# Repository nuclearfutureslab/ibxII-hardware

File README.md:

# IBX ]\[ Hardware

IBX ]\[ is an information barrier setup for nuclear warhead verification with an Apple II ([Details](http://www.vintageverification.org)).
This repository contains schematics and layout files for two custom Apple II peripheral cards.

The KiCad files use the [Apple \]\[ Edge Connector Template](http://www.xjmaas.nl/my-apple-collection/apple-edge-connector-template-for-kicad/), best place it inside the directory as (Apple2_Bus).

## ADC Board
Apple II peripheral card for A/D conversion of signals from radiation detectors (scintillator/photo multiplier combination). The card includes all necessary parts - pre-amplifier, amplification & pulse shaping, peak-detect and hold circuit, ADC timing circuit. The current revision is improved to use full +12V/-12V components all the way to the ADC. Previous versions included 8 LEDs that can be toggled by writing to a specific Apple II memory location, but these have been removed now.

[Rev. 3 Board at OSHPark repository](https://oshpark.com/shared_projects/9M42SHV2)
[Rev. 1 Board at OSHPark repository](https://oshpark.com/shared_projects/9M42SHV2)

### Address scheme (has to be offset by address of card slot, eg. 49344 for Slot 4):

| Address | R/W | Function |
|----| ----|----|
| 01 | (Read) | Reset trigger circuit, make it ready for a new incoming pulse |
| 02 | (Read) | Read low byte of ADC value |
| 03 | (Read) | Read high byte of ADC value |
| 04 | (Read) | Read status buffer for ADC |

## HV Board

Apple II peripheral card to provide high voltage supply to devices (e.g. Photo Multiplier tubes). The voltage is adjustable by writing an 8bit value to a memory address. It produces a voltage from 0-5V depending on this value, which gets converted into highvoltage by a CAEN 7505P module. 

[Rev. 1 Board at OSHPark repository](https://oshpark.com/shared_projects/YkaW1fvx)

### Address scheme (has to be offset by address of card slot, eg. 49312 for Slot 2):

| Address | R/W | Function |
|----| ----|----|
00 | (Write) | Address to write a value for DA
01 | (Read) | enable HV 
02 | (Read) | disable HV

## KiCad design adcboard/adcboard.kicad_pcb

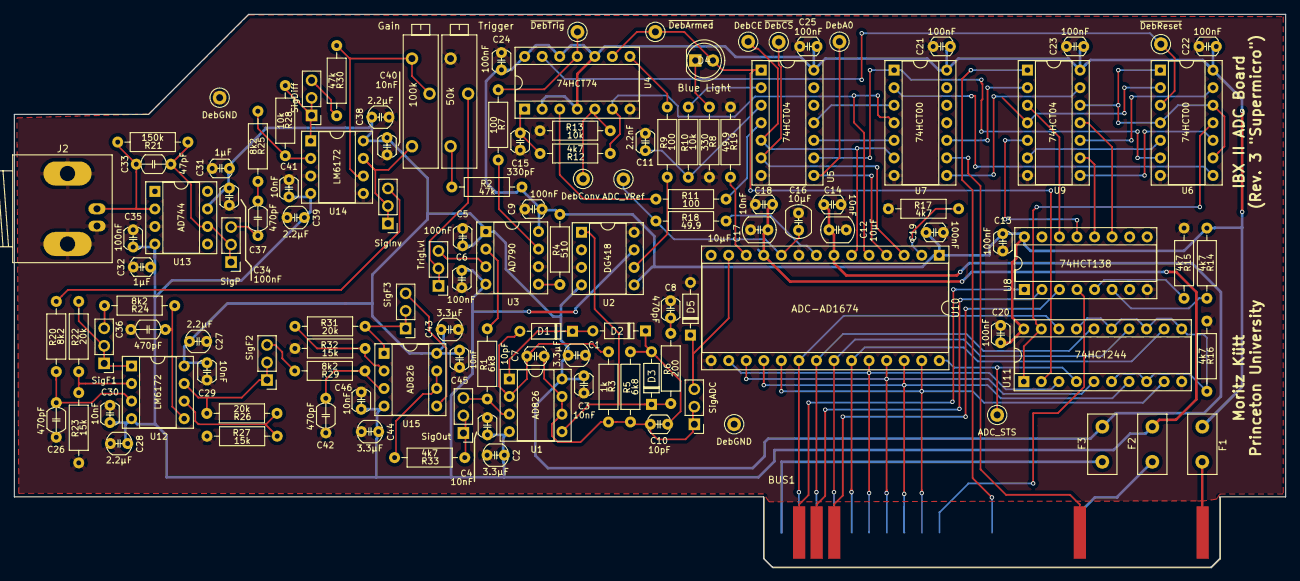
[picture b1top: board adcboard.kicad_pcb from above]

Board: 2 copper layers, 184.0 x 80.0 mm, 126 parts (0 on the bottom side), 99 nets.

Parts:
BUS1: A2_BUS; BUS_ADC
C1, C2, C43, C44: 3.3µF; FG14
C3, C4, C14, C18, C29, C30, C40, C41, C45, C46: 10nF; FG18
C5, C6, C9, C13, C19, C20, C21, C22, C23, C24, C25, C34, C35: 100nF; FG18
C7, C10: 10pF; FG18
C8: 470pF; FG18
C11: 2.2nF; FG18
C12, C16, C17: 10µF; FG16
C15: 330pF; FG18
C26, C36, C37, C42: 470pF; FG28
C27, C28, C38, C39: 2.2µF; FG14
C31, C32: 1µF; FG18
C33: 47pF; FG28
D1, D2, D3: SD103A; D_DO-35_SOD27_P7.62mm_Horizontal
D4: Blue Light; LED_D5.0mm
D5: D_Zener_Small; D_DO-35_SOD27_P7.62mm_Horizontal
F1, F3: HC:250mA; Fuse_Littelfuse_395Series
F2: HC:120mA; Fuse_Littelfuse_395Series
Gain: 100k; Potentiometer_Bourns_3006P_Horizontal
J1: SigOut; 3-Pin-Header
J2: Detector; BNC_Socket_TYCO-AMP_LargePads
J3: TrigLvl; 3-Pin-Header
J4: SigADC; 3-Pin-Header
J5: SigF1; 3-Pin-Header
J6: SigP; 3-Pin-Header
J7: SigF2; 3-Pin-Header
J8: SigDiff; 3-Pin-Header
J9: SigF3; 3-Pin-Header
J10: SigInv; 3-Pin-Header
R1, R5: 6k8; Resistor
R2, R30: 47k; Resistor
R3: 1k; Resistor
R4: 510; Resistor
R6: 200; Resistor
R7, R9, R11: 100; Resistor
R8: 330; Resistor
R10, R13, R28: 10k; Resistor
R12, R14, R15, R16, R17, R33: 4k7; Resistor
R18, R19: 49.9; Resistor
R20, R24, R25, R29: 8k2; Resistor
R21: 150k; Resistor
R22, R26, R31: 20k; Resistor
R23, R27, R32: 15k; Resistor
TP1: ~DebTrig; TP
TP2: ~DebArmed; TP
TP3: ~DebReset; TP
TP4: ADC_VRef; TP
TP5: DebConv; TP
TP6: DebA0; TP
TP7: DebCE; TP
TP8: ~DebCS; TP
TP9, TP10: DebGND; TP
TP11: ADC_STS; TP
Trigger: 50k; Potentiometer_Bourns_3006P_Horizontal
U1, U15: AD826; DIP-8
U2: DG418; DIP-8
U3: AD790; DIP-8
U4: 74HCT74; DIP-14
U5, U9: 74HCT04; DIP-14
U6, U7: 74HCT00; DIP-14
U8: 74HCT138; DIP-16_W7.62mm_Socket
U10: ADC-AD1674; DIP-28_W15.24mm_Socket
U11: 74HCT244; DIP-20_W7.62mm_Socket
U12, U14: LM6172; DIP-8
U13: AD744; DIP-8

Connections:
+5V: C9.2, C13.1, C19.1, C20.2, C21.2, C22.2, C23.2, C24.2, C25.2, F1.1, R2.2, R4.2, R14.1, U2.5, U3.8, U4.2, U4.4, U4.10, U4.12, U4.14, U5.14, U6.14, U7.14, U8.16, U9.14, U10.1, U11.20
+12V: C1.1, C3.2, C5.1, C12.2, C14.1, C27.1, C29.2, C31.1, C34.2, C38.1, C40.2, C43.1, C45.2, F3.2, U1.8, U2.4, U3.1, U10.7, U12.8, U13.7, U14.8, U15.8
-12V: C2.1, C4.2, C6.1, C17.2, C18.1, C28.1, C30.2, C32.1, C35.2, C39.1, C41.2, C44.1, C46.2, F2.2, U1.4, U2.7, U3.4, U10.11, U12.4, U13.4, U14.4, U15.4
/Amplifier/SigDiff: J8.1, J8.2, R28.1, U14.1
/Amplifier/SigDiffb: J8.3, R30.2
/Amplifier/SigF1: J5.1, J5.2, R22.2, U12.1
/Amplifier/SigF1b: J5.3, R24.2
/Amplifier/SigF2: J7.1, J7.2, R26.2, U12.7
/Amplifier/SigF2b: J7.3, R29.2
/Amplifier/SigF3: J9.1, J9.2, R31.2, U15.1
/Amplifier/SigF3b: J9.3, U15.5
/Amplifier/SigInv: Gain.1, J10.1, J10.2, U14.7
/Amplifier/SigInvb: J10.3, R20.2
/Amplifier/SigOut: J1.1, J1.2, R33.1
/Amplifier/SigP: C33.2, J6.1, J6.2, R21.1, U13.6
/Amplifier/SigPb: C37.2, J6.3
/Amplifier/SigRaw: C33.1, J2.1, R21.2, U13.2
A0: BUS1.2, U8.1
A1: BUS1.3, U8.2
A2: BUS1.4, U8.3
D0: BUS1.49, U10.20, U11.18
D1: BUS1.48, U10.21, U11.16
D2: BUS1.47, U10.22, U11.14
D3: BUS1.46, U10.23, U11.12
D4: BUS1.45, U10.16, U10.24, U11.3
D5: BUS1.44, U10.17, U10.25, U11.5
D6: BUS1.43, U10.18, U10.26, U11.7
D7: BUS1.42, U10.19, U10.27, U11.9
GND: BUS1.26, C1.2, C2.2, C3.1, C4.1, C5.2, C6.2, C8.1, C9.1, C11.1, C12.1, C13.2, C14.2, C15.1, C16.1, C17.1, C18.2, C19.2, C20.1, C21.1, C22.1, C23.1, C24.1, C25.1, C26.1, C27.2, C28.2, C29.1, C30.1, C31.2, C32.2, C34.1, C35.1, C36.1, C38.2, C39.2, C40.1, C41.1, C42.1, C43.2, C44.2, C45.1, C46.1, D5.2, J2.2, R8.2, R13.1, R15.1, R16.1, R17.1, R19.1, R23.1, R27.1, R32.1, TP9.1, TP10.1, Trigger.3, U2.3, U2.8, U3.6, U4.7, U5.7, U6.7, U7.7, U8.8, U9.7, U10.9, U10.15, U11.10, U13.3, U14.3, U14.5
unnamed: BUS1.25, F1.2
unnamed: BUS1.33, F2.1
unnamed: BUS1.50, F3.1
unnamed: C7.1, D1.2, R3.1, U1.2
unnamed: C8.2, R6.2
unnamed: C10.1, D2.1, D3.2, R5.2
unnamed: C7.2, C10.2, J4.1, J4.2, R3.2, R5.1, U1.6, U1.7
unnamed: C11.2, R10.1, U5.3
unnamed: C15.2, R12.2, U4.1
unnamed: C16.2, R18.1, TP4.1, U10.10
unnamed: C26.2, R20.1, U12.3
unnamed: C36.2, R24.1, U12.5
unnamed: C37.1, R25.2
unnamed: C42.2, R29.1, U15.3
unnamed: D1.1, D2.2, U1.1
unnamed: D3.1, R6.1, U1.5, U2.1
unnamed: D4.1, R8.1
unnamed: D5.1, J4.3, U10.13
unnamed: J1.3, R1.1, U1.3
unnamed: J3.1, J3.2, Trigger.2
unnamed: J3.3, U3.3
unnamed: R1.2, U3.2
unnamed: R2.1, Trigger.1
unnamed: R4.1, U3.5
unnamed: R7.1, TP1.1, U4.11
unnamed: R7.2, U3.7
unnamed: R9.1, U2.6
unnamed: R9.2, U4.8
unnamed: R10.2, U5.2
unnamed: R11.1, U4.3
unnamed: R11.2, U5.4
unnamed: R12.1, U4.6, U7.4, U10.5
unnamed: R13.2, TP5.1, U4.5
unnamed: R14.2, U8.6
unnamed: R15.2, U8.5
unnamed: R16.2, U11.6, U11.8, U11.11, U11.13, U11.15, U11.17
unnamed: R17.2, U10.2
unnamed: R18.2, U10.8
unnamed: R19.2, U10.12
unnamed: R22.1, R23.2, U12.2
unnamed: R25.1, R28.2, U14.2
unnamed: R26.1, R27.2, U12.6
unnamed: Gain.2, Gain.3, R30.1, U14.6
unnamed: R31.1, R32.2, U15.2
unnamed: R33.2, U15.6, U15.7
unnamed: TP3.1, U4.13, U6.3
unnamed: TP6.1, U5.8, U10.4
unnamed: TP7.1, U5.5, U7.6, U10.6
unnamed: TP8.1, U5.6, U10.3
unnamed: TP11.1, U10.28, U11.4
unnamed: U5.9, U6.6, U7.1
unnamed: U5.10, U7.5
unnamed: U5.11, U7.3
unnamed: U6.8, U7.2
unnamed: U7.8, U9.13
unnamed: U7.10, U9.2
unnamed: U8.11, U9.11
unnamed: U8.12, U9.9
unnamed: U8.13, U9.5
unnamed: U8.14, U9.3
O1: U6.2, U9.4
O2: U6.5, U9.6
O3: U6.10, U9.8
O4: U6.13, U9.10
Phi1: BUS1.38, U9.1
R/~W: BUS1.18, U7.9
RD: U6.1, U6.4, U6.9, U6.12, U9.12
~Armed: D4.2, TP2.1, U4.9, U5.1, U11.2
~BufferOE: U6.11, U11.1, U11.19
~DevSel: BUS1.41, U8.4

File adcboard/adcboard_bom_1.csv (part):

Component,Description,Part,References,Value,Footprint,Quantity Per PCB,Datasheet,DigiKey
1,,A2_BUS,BUS1,A2_BUS,BUS_ADC,1,,
2,"Unpolarized capacitor, small symbol",C_Small,C5 C6 C9 C13 C19 C20 C21 C22 C23 C24 C25 C34 C35,100nF,FG18,13,https://product.tdk.com/info/en/documents/chara_sheet/FG18X7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,445-173265-1-ND
3,"Unpolarized capacitor, small symbol",C_Small,C3 C4 C14 C18 C29 C30 C40 C41 C45 C46,10nF,FG18,10,https://product.tdk.com/info/en/documents/chara_sheet/FG18X7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,445-173172-1-ND
4,"Unpolarized capacitor, small symbol",C_Small,C7 C10,10pF,FG18,2,https://product.tdk.com/info/en/documents/chara_sheet/FG18C0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,445-173169-1-ND
5,"Unpolarized capacitor, small symbol",C_Small,C12 C16 C17,10µF,FG16,3,https://product.tdk.com/info/en/documents/chara_sheet/FG16X5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,445-173153-1-ND
6,"Unpolarized capacitor, small symbol",C_Small,C31 C32,1µF,FG18,2,https://product.tdk.com/info/en/documents/chara_sheet/FG18X5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,445-173257-1-ND
7,"Unpolarized capacitor, small symbol",C_Small,C11,2.2nF,FG18,1,https://product.tdk.com/info/en/documents/chara_sheet/FG18C0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,445-173184-1-ND
8,"Unpolarized capacitor, small symbol",C_Small,C27 C28 C38 C39,2.2µF,FG14,4,https://product.tdk.com/info/en/documents/chara_sheet/FG14X7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,445-173138-1-ND
9,"Unpolarized capacitor, small symbol",C_Small,C1 C2 C43 C44,3.3µF,FG14,4,https://product.tdk.com/info/en/documents/chara_sheet/FG14X5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,445-173130-1-ND
10,"Unpolarized capacitor, small symbol",C_Small,C15,330pF,FG18,1,https://product.tdk.com/info/en/documents/chara_sheet/FG18C0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,445-173190-1-ND
11,"Unpolarized capacitor, small symbol",C_Small,C26 C36 C37 C42,470pF,FG28,4,https://product.tdk.com/info/en/documents/chara_sheet/FG28C0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,445-173500-1-ND
12,"Unpolarized capacitor, small symbol",C_Small,C8,470pF,FG18,1,https://product.tdk.com/info/en/documents/chara_sheet/FG18C0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,445-173197-1-ND
13,"Unpolarized capacitor, small symbol",C_Small,C33,47pF,FG28,1,https://product.tdk.com/info/en/documents/chara_sheet/FG28C0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,445-173499-1-ND
14,"Zener diode, small symbol",D_Zener_Small,D5,D_Zener_Small,D_DO-35_SOD27_P7.62mm_Horizontal,1,http://www.vishay.com/docs/85604/bzx55-se.pdf,BZX55B10-TRGICT-ND
15,"Light emitting diode, small symbol",LED_Small,D4,LED_Small,LED_D5.0mm,1,https://www.lumex.com/content/files/ProductAttachment/SSL-LX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,67-1751-ND
16,"Schottky diode, small symbol",D_Schottky_Small,D1 D2 D3,SD103A,D_DO-35_SOD27_P7.62mm_Horizontal,3,http://www.vishay.com/docs/85754/sd103a.pdf,SD103AVSCT-ND
17,"Resettable fuse, polymeric positive temperature coefficient, small symbol",Polyfuse_Small,F2,HC:120mA,Fuse_Littelfuse_395Series,1,https://product.tdk.com/info/en/documents/data_sheet/55/db/P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,495-3907-ND
18,"Resettable fuse, polymeric positive temperature coefficient, small symbol",Polyfuse_Small,F1 F3,HC:250mA,Fuse_Littelfuse_395Series,2,https://product.tdk.com/info/en/documents/data_sheet/55/db/P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,495-3904-ND
19,"coaxial connector (BNC, SMA, SMB, SMC, Cinch/RCA, ...)",Conn_Coaxial,J2,Detector,BNC_Socket_TYCO-AMP_LargePads,1,https://www.te.com/commerce/DocumentDelivery/DDEController?A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,A97555-ND
20,"Generic connector, single row, 01x03, script generated (kicad-library-utils/schlib/autogen/connector/)",Conn_01x03,J4,SigADC,3-Pin-Header,1,~,
21,"Generic connector, single row, 01x03, script generated (kicad-library-utils/schlib/autogen/connector/)",Conn_01x03,J8,SigDiff,3-Pin-Header,1,~,
22,"Generic connector, single row, 01x03, script generated (kicad-library-utils/schlib/autogen/connector/)",Conn_01x03,J5,SigF1,3-Pin-Header,1,~,
23,"Generic connector, single row, 01x03, script generated (kicad-library-utils/schlib/autogen/connector/)",Conn_01x03,J7,SigF2,3-Pin-Header,1,~,
24,"Generic connector, single row, 01x03, script generated (kicad-library-utils/schlib/autogen/connector/)",Conn_01x03,J9,SigF3,3-Pin-Header,1,~,
25,"Generic connector, single row, 01x03, script generated (kicad-library-utils/schlib/autogen/connector/)",Conn_01x03,J10,SigInv,3-Pin-Header,1,~,
26,"Generic connector, single row, 01x03, script generated (kicad-library-utils/schlib/autogen/connector/)",Conn_01x03,J1,SigOut,3-Pin-Header,1,~,
27,"Generic connector, single row, 01x03, script generated (kicad-library-utils/schlib/autogen/connector/)",Conn_01x03,J6,SigP,3-Pin-Header,1,~,
28,"Generic connector, single row, 01x03, script generated (kicad-library-utils/schlib/autogen/connector/)",Conn_01x03,J3,TrigLvl,3-Pin-Header,1,~,
29,"Resistor, small symbol",R_Small,R7 R9 R11,100,Resistor,3,http://www.vishay.com/docs/28724/mrs16m25.pdf,BC3952CT-ND
30,"Resistor, small symbol",R_Small,R10 R13 R28,10k,Resistor,3,http://www.vishay.com/docs/28724/mrs16m25.pdf,PPC10.0KZCT-ND
31,"Resistor, small symbol",R_Small,R21,150k,Resistor,1,http://www.vishay.com/docs/28724/mrs16m25.pdf,PPC150KZCT-ND
32,"Resistor, small symbol",R_Small,R23 R27 R32,15k,Resistor,3,http://www.vishay.com/docs/28724/mrs16m25.pdf,BC4005CT-ND
33,"Resistor, small symbol",R_Small,R3,1k,Resistor,1,http://www.vishay.com/docs/28724/mrs16m25.pdf,PPC1.00KZCT-ND
34,"Resistor, small symbol",R_Small,R6,200,Resistor,1,http://www.vishay.com/docs/28724/mrs16m25.pdf,BC4039CT-ND
35,"Resistor, small symbol",R_Small,R22 R26 R31,20k,Resistor,3,http://www.vishay.com/docs/28724/mrs16m25.pdf,PPC20.0KZCT-ND
36,"Resistor, small symbol",R_Small,R8,330,Resistor,1,http://www.vishay.com/docs/28724/mrs16m25.pdf,BC4123CT-ND
37,"Resistor, small symbol",R_Small,R2 R30,47k,Resistor,2,http://www.vishay.com/docs/28724/mrs16m25.pdf,BC4178CT-ND
38,"Resistor, small symbol",R_Small,R18 R19,49.9,Resistor,2,http://www.vishay.com/docs/28724/mrs16m25.pdf,BC4639CT-ND
39,"Resistor, small symbol",R_Small,R12 R14 R15 R16 R17 R33,4k7,Resistor,6,http://www.vishay.com/docs/28724/mrs16m25.pdf,BC4176CT-ND
40,"Resistor, small symbol",R_Small,R4,510,Resistor,1,http://www.vishay.com/docs/28724/mrs16m25.pdf,BC4190CT-ND
41,"Resistor, small symbol",R_Small,R1 R5,6k8,Resistor,2,http://www.vishay.com/docs/28724/mrs16m25.pdf,BC4239CT-ND
42,"Resistor, small symbol",R_Small,R20 R24 R25 R29,8k2,Resistor,4,http://www.vishay.com/docs/28724/mrs16m25.pdf,BC4264CT-ND
43,Potentiometer,R_POT,RV2,100k,Potentiometer_Bourns_3006P_Horizontal,1,https://www.bourns.com/docs/Product-Datasheets/3006.pdf,3006P-104LF-ND
44,Potentiometer,R_POT,RV1,50k,Potentiometer_Bourns_3006P_Horizontal,1,https://www.bourns.com/docs/Product-Datasheets/3006.pdf,3006P-503LF-ND
45,quad 2-input NAND gate,7400,U6 U7,74HCT00,DIP-14,2,http://www.ti.com/lit/ds/symlink/cd74hc74.pdf,296-2081-5-ND
46,hex inverter,74HC04,U5 U9,74HCT04,DIP-14,2,http://www.ti.com/lit/ds/symlink/cd74hc04.pdf,296-2083-5-ND
47,Decoder 3 to 8 active low outputs,74LS138,U8,74HCT138,DIP-16_W7.62mm_Socket,1,http://www.ti.com/lit/ds/symlink/cd74hc138.pdf,296-2091-5-ND
48,8-bit Buffer/Line Driver 3-state,74HC244,U11,74HCT244,DIP-20_W7.62mm_Socket,1,http://www.ti.com/lit/ds/symlink/cd74hc240.pdf,296-2104-5-ND
49,"Dual D Flip-flop, Set & Reset",74HC74,U4,74HCT74,DIP-14,1,http://www.ti.com/lit/ds/symlink/cd74hc74.pdf,296-2132-5-ND
50,"Single Rail-to-Rail High Output Current Operational Amplifiers, SOIC-8",OP179GS,U13,AD744,DIP-8,1,http://www.analog.com/media/en/technical-documentation/data-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,AD744KNZ-ND
51,,AD790,U3,AD790,DIP-8,1,https://www.analog.com/media/en/technical-documentation/data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,AD790JNZ-ND
52,Dual operational amplifier,Opamp_Dual_Generic,U1,AD826,DIP-8,1,https://www.analog.com/media/en/technical-documentation/data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,AD826ANZ-ND
53,"Dual High Speed, Low Power, Low Distortion, Voltage Feedback Amplifiers, DIP-8/SOIC-8",LM6172,U15,AD826,DIP-8,1,https://www.analog.com/media/en/technical-documentation/data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,AD826ANZ-ND
54,,ADC-AD1674,U10,ADC-AD1674,DIP-28_W15.24mm_Socket,1,https://www.analog.com/media/en/technical-documentation/data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,AD1674JNZ-ND
55,"Single SPST Monolithic CMOS Analog Switch, normally OFF, 20Ohm Ron, DIP-8",DG418xJ,U2,DG418,DIP-8,1,http://www.vishay.com/docs/70051/dg417.pdf,DG418DJ-E3-ND
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
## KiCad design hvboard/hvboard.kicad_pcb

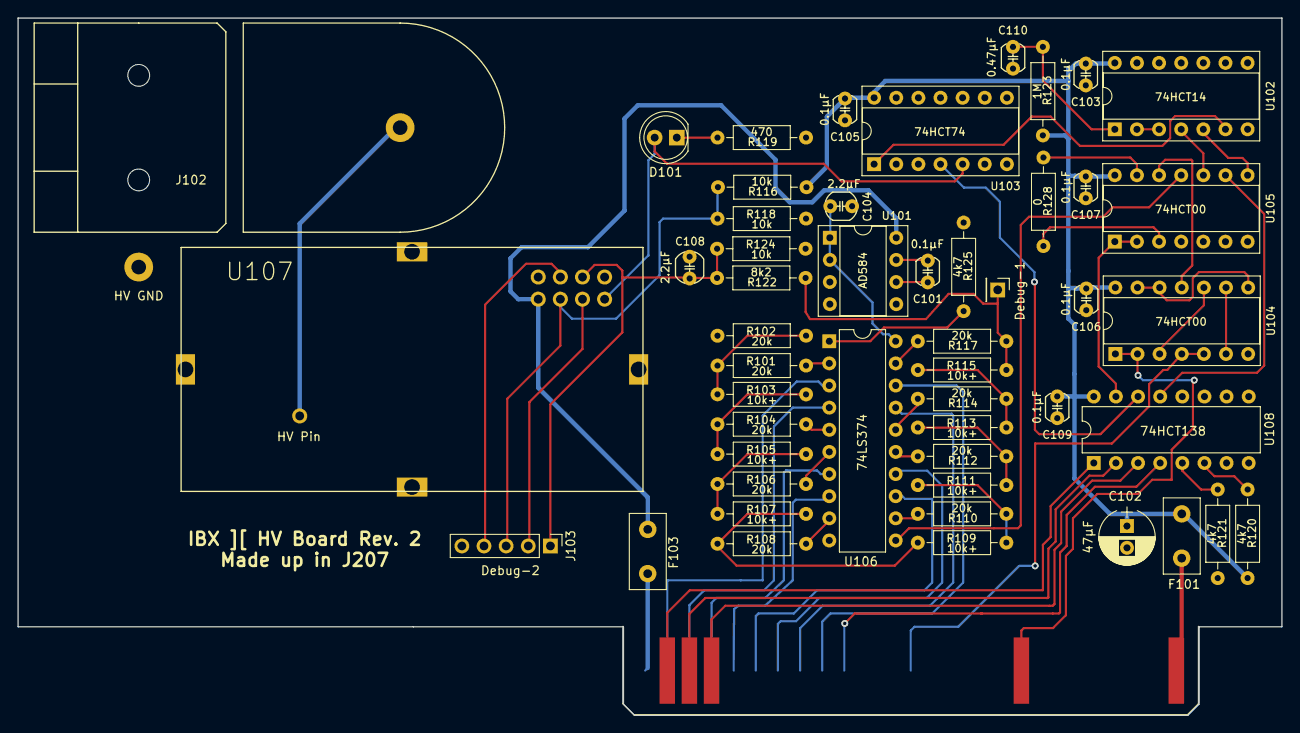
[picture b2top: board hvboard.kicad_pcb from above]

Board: 2 copper layers, 145.0 x 80.0 mm, 51 parts (0 on the bottom side), 63 nets.

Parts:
BUS101: A2_BUS; BUS_A2
C101, C103, C105, C106, C107, C109: 0.1µF; FG18
C102: 47µF; CP_Radial_D6.3mm_P2.50mm
C104, C108: 2.2µF; FG14
C110: 0.47µF; FG18
D101: LED; LED_D5.0mm
F101, F103: Polyfuse_Small; Fuse_TE5_Littlefuse-395Series
J101: Debug-1; Socket_Strip_Straight_1x01_Pitch2.54mm
J102: HV; HVConnector3D
J103: Debug-2; Pin_Header_Straight_1x05_Pitch2.54mm
R101, R102, R104, R106, R108, R110, R112, R114, R117: 20k; Resistor
R103, R105, R107, R109, R111, R113, R115: 10k+; Resistor
R116, R118, R124: 10k; Resistor
R119: 470; Resistor
R120, R121, R125: 4k7; Resistor
R122: 8k2; Resistor
R123: 1M; Resistor
R128: 0; Resistor
U101: AD584; DIP-8
U102: 74HCT14; DIP-14
U103: 74HCT74; DIP-14
U104, U105: 74HCT00; DIP-14
U106: 74LS374; DIP-20_W7.62mm
U107: CHV; CHV-rev2
U108: 74HCT138; DIP-16_W7.62mm

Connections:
+5V: C102.1, C103.2, C105.2, C106.2, C107.2, C109.2, F101.1, R116.1, R120.2, R123.2, U102.14, U103.14, U104.14, U105.14, U108.16
+12V: F103.1, U101.8, U107.7
/D0: BUS101.49, U106.3
/D1: BUS101.48, U106.4
/D2: BUS101.47, U106.7
/D3: BUS101.46, U106.8
/D4: BUS101.45, U106.13
/D5: BUS101.44, U106.14
/D6: BUS101.43, U106.17
/D7: BUS101.42, U106.18
GND: BUS101.26, C102.2, C103.1, C104.1, C105.1, C106.1, C107.1, C108.1, C109.1, C110.2, J102.2, J103.5, R102.1, R118.2, R119.1, R121.2, R124.2, R125.1, U101.4, U102.7, U103.2, U103.3, U103.7, U104.7, U105.7, U106.10, U107.8, U107.S1, U107.S2, U107.S3, U107.S4, U108.8
unnamed: BUS101.2, U108.1
unnamed: BUS101.3, U108.2
unnamed: BUS101.4, U108.3
unnamed: BUS101.18, U104.1, U104.2
unnamed: BUS101.25, F101.2
unnamed: BUS101.38, U104.4, U104.5
unnamed: BUS101.41, U108.4
unnamed: BUS101.50, F103.2
unnamed: C101.1, U101.6
unnamed: C101.2, U101.7
unnamed: C104.2, U101.1, U101.2, U106.20
unnamed: C108.2, J103.1, R122.2, R124.1, U107.4
unnamed: C110.1, R123.1, U102.1
unnamed: D101.1, R119.2
unnamed: D101.2, U103.5, U107.1
unnamed: J101.1, R115.2, R117.1, R122.1
unnamed: J102.1, U107.9
unnamed: J103.2, U107.3
unnamed: J103.3, R116.2, R118.1, U107.5
unnamed: J103.4, U107.6
unnamed: R101.1, R102.2, R103.1
unnamed: R101.2, U106.2
unnamed: R103.2, R104.1, R105.1
unnamed: R104.2, U106.5
unnamed: R105.2, R106.1, R107.1
unnamed: R106.2, U106.6
unnamed: R107.2, R108.1, R109.1
unnamed: R108.2, U106.9
unnamed: R109.2, R110.1, R111.1
unnamed: R110.2, U106.12
unnamed: R111.2, R112.1, R113.1
unnamed: R112.2, U106.15
unnamed: R113.2, R114.1, R115.1
unnamed: R114.2, U106.16
unnamed: R117.2, U106.19
unnamed: R120.1, U108.6
unnamed: R121.1, U108.5
unnamed: R125.2, U106.1
unnamed: R128.1, U105.13
unnamed: R128.2, U105.3
unnamed: U102.2, U102.3
unnamed: U102.4, U105.10
unnamed: U102.5, U105.8
unnamed: U102.6, U103.1
unnamed: U103.4, U108.14
unnamed: U104.6, U104.9
unnamed: U104.3, U104.10
unnamed: U104.11, U105.12
unnamed: U104.8, U104.12, U104.13
unnamed: U105.1, U105.2, U108.15
unnamed: U105.9, U108.13
unnamed: U105.11, U106.11

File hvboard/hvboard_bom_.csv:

Component,Description,Part,References,Value,Footprint,Quantity Per PCB,Datasheet,DigiKey
1,,A2_BUS,BUS101,A2_BUS,BUS_A2,1,,
2,"Unpolarized capacitor, small symbol",C_Small,C101 C103 C105 C106 C107 C109,0.1µF,FG18,6,https://product.tdk.com/info/en/documents/chara_sheet/FG18X7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,445-173265-1-ND
3,"Unpolarized capacitor, small symbol",C_Small,C110,0.47µF,FG18,1,https://product.tdk.com/info/en/documents/chara_sheet/FG18X7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,445-173276-1-ND
4,"Unpolarized capacitor, small symbol",C_Small,C104 C108,2.2µF,FG14,2,https://product.tdk.com/info/en/documents/chara_sheet/FG14X7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,445-173138-1-ND
5,"Polarized capacitor, small US symbol",CP1_Small,C102,47µF,CP_Radial_D6.3mm_P2.50mm,1,https://industrial.panasonic.com/cdbs/www-data/pdf/RDF0000/A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,P15400-ND
6,Light emitting diode,LED,D101,LED,LED_D5.0mm,1,https://www.lumex.com/content/files/ProductAttachment/SSL-LX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,67-2288-ND
7,"Resettable fuse, polymeric positive temperature coefficient, small symbol",Polyfuse_Small,F101 F103,Polyfuse_Small,Fuse_TE5_Littlefuse-395Series,2,https://product.tdk.com/info/en/documents/data_sheet/55/db/P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,495-3904-ND
8,"Generic connector, single row, 01x01, script generated (kicad-library-utils/schlib/autogen/connector/)",Conn_01x01,J101,Debug-1,Socket_Strip_Straight_1x01_Pitch2.54mm,1,,
9,"Generic connector, single row, 01x05, script generated (kicad-library-utils/schlib/autogen/connector/)",Conn_01x05,J103,Debug-2,Pin_Header_Straight_1x05_Pitch2.54mm,1,,
10,"coaxial connector (BNC, SMA, SMB, SMC, Cinch/RCA, ...)",Conn_Coaxial,J102,HV,HVConnector3D,1,,
11,"Resistor, small symbol",R_Small,R128,0,Resistor,1,,
12,Resistor,R,R116 R118 R124,10k,Resistor,3,http://www.vishay.com/docs/28724/mrs16m25.pdf,PPC10.0KZCT-ND
13,Resistor,R,R103 R105 R107 R109 R111 R113 R115,10k+,Resistor,7,http://www.vishay.com/docs/28767/mbsmapre.pdf,BC4515CT-ND
14,"Resistor, small symbol",R_Small,R123,1M,Resistor,1,http://www.vishay.com/docs/28724/mrs16m25.pdf,BC3959CT-ND
15,Resistor,R,R101 R102 R104 R106 R108 R110 R112 R114 R117,20k,Resistor,9,http://www.vishay.com/docs/28767/mbsmapre.pdf,BC4511CT-ND
16,"Resistor, small symbol",R_Small,R119,470,Resistor,1,http://www.vishay.com/docs/28724/mrs16m25.pdf,BC4173CT-ND
17,"Resistor, small symbol",R_Small,R120 R121 R125,4k7,Resistor,3,http://www.vishay.com/docs/28724/mrs16m25.pdf,BC4176CT-ND
18,Resistor,R,R122,8k2,Resistor,1,http://www.vishay.com/docs/28724/mrs16m25.pdf,BC4264CT-ND
19,quad 2-input NAND gate,7400,U104 U105,74HCT00,DIP-14,2,http://www.ti.com/lit/gpn/sn74ls00,296-2081-5-ND
20,Decoder 3 to 8 active low outputs,74LS138,U108,74HCT138,DIP-16_W7.62mm,1,http://www.ti.com/lit/ds/symlink/cd74hc138.pdf,296-2091-5-ND
21,Hex inverter schmitt trigger,74HC14,U102,74HCT14,DIP-14,1,http://www.nxp.com/documents/data_sheet/74HC_HCT04.pdf,296-2093-5-ND
22,"Dual D Flip-flop, Set & Reset",74HC74,U103,74HCT74,DIP-14,1,http://www.ti.com/lit/ds/symlink/cd74hc74.pdf,296-2132-5-ND
23,"8-bit Register, 3-state outputs",74LS374,U106,74LS374,DIP-20_W7.62mm,1,http://www.ti.com/lit/ds/symlink/cd74hct374.pdf,296-2115-5-ND
24,,AD584,U101,AD584,DIP-8,1,https://www.analog.com/media/en/technical-documentation/data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,AD584KNZ-ND
25,,CHV,U107,CHV,CHV-rev2,1,,





Component Groups:,25
Component Count:,51
Fitted Components:,51
Number of PCBs:,1
Total components:,51
Schematic Version:,
Schematic Date:,
BoM Date:,Wed 09 Jan 2019 12:07:31 AM EST
Schematic Source:,/home/moritz/Sync/gdrive_princeton/workprojects/vintageibx/appleIIdev/ibxII-hardware/hvboard/hvboard.sch
KiCad Version:,Eeschema 5.0.2-bee76a0~70~ubuntu18.04.1

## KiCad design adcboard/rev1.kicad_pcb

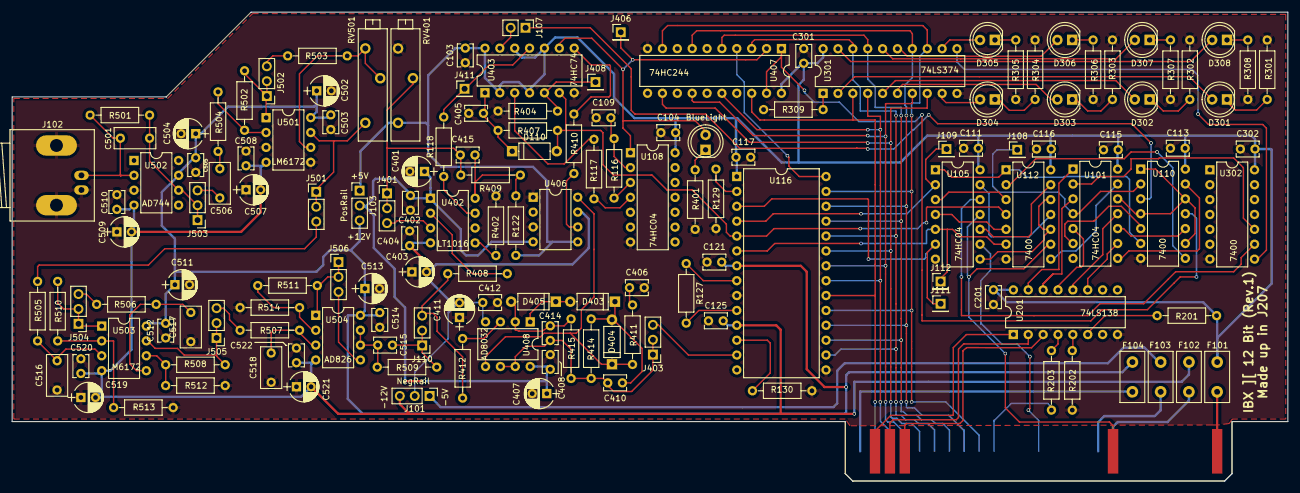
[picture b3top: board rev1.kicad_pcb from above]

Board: 2 copper layers, 217.8 x 80.1 mm, 150 parts (0 on the bottom side), 128 nets.

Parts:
BUS101: A2_BUS; BUS_A2
BlueLight: LED_Small; LED_D5.0mm
C103, C104, C111, C113, C115, C116, C117, C121, C125, C201, C301, C302: 2.2µF; C_Disc_D3.8mm_W2.6mm_P2.50mm
C109, C415: 100pF; C_Disc_D3.8mm_W2.6mm_P2.50mm
C401, C403, C407, C411, C504, C509: 10µF; CP_Radial_D5.0mm_P2.50mm
C402, C404, C408, C412, C505, C510, C514, C515, C522: 10nF; C_Disc_D3.8mm_W2.6mm_P2.50mm
C405: 150pF; C_Disc_D3.8mm_W2.6mm_P2.50mm
C406: 470pF; C_Disc_D3.8mm_W2.6mm_P2.50mm
C410, C414: 10pF; C_Disc_D3.8mm_W2.6mm_P2.50mm
C501, C506, C516, C517, C518: 470pF; C_Rect_L7.0mm_W3.5mm_P5.00mm
C502, C507, C511, C513, C519, C521: 2.2µF; CP_Radial_D5.0mm_P2.50mm
C503, C508, C512, C520: 100nF; C_Disc_D3.8mm_W2.6mm_P2.50mm
D110: D_Small; D_A-405_P7.62mm_Horizontal
D301, D302, D303, D304, D305, D306, D307, D308: LED; LED_D5.0mm
D403, D404, D405: D; D_A-405_P7.62mm_Horizontal
F101, F104: HC:250mA; Fuse_TE5_Littlefuse-395Series
F102, F103: HC:160mA; Fuse_TE5_Littlefuse-395Series
J101: NegRail; Pin_Header_Straight_1x03_Pitch2.54mm
J102: Detector; BNC_Socket_TYCO-AMP_LargePads
J103: PosRail; Pin_Header_Straight_1x03_Pitch2.54mm
J107: FFRst; Pin_Header_Straight_1x02_Pitch2.54mm
J108: ~DebReset; Socket_Strip_Straight_1x01_Pitch2.54mm
J109: ~DebA0; Socket_Strip_Straight_1x01_Pitch2.54mm
J110: SigOut; Pin_Header_Straight_1x03_Pitch2.54mm
J111: ~DebCS; Socket_Strip_Straight_1x01_Pitch2.54mm
J112: DebCE; Socket_Strip_Straight_1x01_Pitch2.54mm
J401: TrigLvl; Pin_Header_Straight_1x03_Pitch2.54mm
J403: SigADC; Pin_Header_Straight_1x03_Pitch2.54mm
J406: ~DebArmed; Socket_Strip_Straight_1x01_Pitch2.54mm
J408: DebConv; Socket_Strip_Straight_1x01_Pitch2.54mm
J411: ~DebTrig; Socket_Strip_Straight_1x01_Pitch2.54mm
J501: SigInv; Pin_Header_Straight_1x03_Pitch2.54mm
J502: SigDiff; Pin_Header_Straight_1x03_Pitch2.54mm
J503: Sig1; Pin_Header_Straight_1x03_Pitch2.54mm
J504: SigF1; Pin_Header_Straight_1x03_Pitch2.54mm
J505: SigF2; Pin_Header_Straight_1x03_Pitch2.54mm
J506: SigF3; Pin_Header_Straight_1x03_Pitch2.54mm
R116, R404, R502: 10k; R_Axial_DIN0207_L6.3mm_D2.5mm_P10.16mm_Horizontal
R117, R118, R410, R412: 100; R_Axial_DIN0207_L6.3mm_D2.5mm_P10.16mm_Horizontal
R122: 0(J); R_Axial_DIN0207_L6.3mm_D2.5mm_P10.16mm_Horizontal
R127, R130: 50; R_Axial_DIN0207_L6.3mm_D2.5mm_P10.16mm_Horizontal
R129, R201, R202, R309, R402, R407, R509: 4k7; R_Axial_DIN0207_L6.3mm_D2.5mm_P10.16mm_Horizontal
R203: 0 (J); R_Axial_DIN0207_L6.3mm_D2.5mm_P10.16mm_Horizontal
R301, R302, R303, R304, R305, R306, R307, R308, R401: 330; R_Axial_DIN0207_L6.3mm_D2.5mm_P10.16mm_Horizontal
R408, R414: 6k2; R_Axial_DIN0207_L6.3mm_D2.5mm_P10.16mm_Horizontal
R409: 100k; R_Axial_DIN0207_L6.3mm_D2.5mm_P10.16mm_Horizontal
R411: 220; R_Axial_DIN0207_L6.3mm_D2.5mm_P10.16mm_Horizontal
R415: 1k; R_Axial_DIN0207_L6.3mm_D2.5mm_P10.16mm_Horizontal
R501: 150k; R_Axial_DIN0207_L6.3mm_D2.5mm_P10.16mm_Horizontal
R503: 47k; R_Axial_DIN0207_L6.3mm_D2.5mm_P10.16mm_Horizontal
R504, R505, R506, R507: 6k8; R_Axial_DIN0207_L6.3mm_D2.5mm_P10.16mm_Horizontal
R508, R510, R511: 20k; R_Axial_DIN0207_L6.3mm_D2.5mm_P10.16mm_Horizontal
R512, R513, R514: 15k; R_Axial_DIN0207_L6.3mm_D2.5mm_P10.16mm_Horizontal
RV401: 50k; Potentiometer_Trimmer_Bourns_3006P
RV501: 100k; Potentiometer_Trimmer_Bourns_3006P
U101, U105, U108: 74HC04; DIP-14_W7.62mm
U110, U112, U302: 7400; DIP-14_W7.62mm
U116: ADC-AD1674; DIP-28_W15.24mm
U201: 74LS138; DIP-16_W7.62mm
U301: 74LS374; DIP-20_W7.62mm
U402: LT1016; DIP-8_W7.62mm
U403: 74HC74; DIP-14_W7.62mm
U406: DG418; DIP-8_W7.62mm
U407: 74HC244; DIP-20_W7.62mm
U408: AD8032; DIP-8_W7.62mm
U501, U503: LM6172; DIP-8_W7.62mm
U502: AD744; DIP-8_W7.62mm
U504: AD826; DIP-8_W7.62mm

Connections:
+5V: C103.2, C104.2, C111.2, C113.2, C115.2, C116.2, C117.1, C201.2, C301.2, C302.2, F101.1, J103.1, R122.1, R201.1, RV401.1, U101.14, U105.14, U108.14, U110.14, U112.14, U116.1, U201.16, U301.20, U302.14, U403.2, U403.4, U403.10, U403.12, U403.14, U406.5, U407.20
+12V: C121.2, C502.1, C503.2, C504.1, C505.2, C511.1, C512.2, C513.1, C514.2, F104.2, J103.3, U116.7, U501.8, U502.7, U503.8, U504.8
+Rail: C401.1, C402.2, C407.1, C408.2, J103.2, U402.1, U406.4, U408.8
-5V: F103.2, J101.1
-12V: C125.2, C507.2, C508.2, C509.2, C510.2, C519.2, C520.2, C521.2, C522.2, F102.2, J101.3, U116.11, U501.4, U502.4, U503.4, U504.4
-Rail: C403.2, C404.2, C411.2, C412.2, J101.2, U402.4, U406.7, U408.4
/Amplifier/SigDiff: J502.1, J502.2, R502.1, U501.1
/Amplifier/SigDiffb: J502.3, R503.2
/Amplifier/SigF1: J504.1, J504.2, R510.2, U503.1
/Amplifier/SigF1b: J504.3, R506.2
/Amplifier/SigF2: J505.1, J505.2, R508.2, U503.7
/Amplifier/SigF2b: J505.3, R507.2
/Amplifier/SigF3: J506.1, J506.2, R511.2, U504.1
/Amplifier/SigF3b: J506.3, U504.5
/Amplifier/SigInv: J501.1, J501.2, RV501.1, U501.7
/Amplifier/SigInvb: J501.3, R505.2
/Amplifier/SigOut: C515.1, J110.1, J110.2, R509.1
/Amplifier/SigP: C501.1, J503.1, J503.2, R501.1, U502.6
/Amplifier/SigPb: C506.2, J503.3
/Amplifier/SigRaw: C501.2, J102.1, R501.2, U502.2
/LED/O0: U101.2, U302.10
A0: BUS101.2, U201.1
A1: BUS101.3, U201.2
A2: BUS101.4, U201.3
D0: BUS101.49, U116.20, U301.3, U407.18
D1: BUS101.48, U116.21, U301.4, U407.16
D2: BUS101.47, U116.22, U301.7, U407.14
D3: BUS101.46, U116.23, U301.8, U407.12
D4: BUS101.45, U116.16, U116.24, U301.18, U407.3
D5: BUS101.44, U116.17, U116.25, U301.17, U407.5
D6: BUS101.43, U116.18, U116.26, U301.14, U407.7
D7: BUS101.42, U116.19, U116.27, U301.13, U407.9
GND: BUS101.26, C103.1, C104.1, C109.1, C111.1, C113.1, C115.1, C116.1, C117.2, C121.1, C125.1, C201.1, C301.1, C302.1, C401.2, C402.1, C403.1, C404.1, C405.2, C406.2, C407.2, C408.1, C411.1, C412.1, C502.2, C503.1, C504.2, C505.1, C507.1, C508.1, C509.1, C510.1, C511.2, C512.1, C513.2, C514.1, C516.1, C517.1, C518.1, C519.1, C520.1, C521.1, C522.1, J102.2, R129.2, R130.2, R202.2, R301.1, R302.1, R303.1, R304.1, R305.1, R306.1, R307.1, R308.1, R309.2, R401.1, R402.1, R404.1, R512.2, R513.2, R514.2, RV401.3, U101.7, U105.7, U108.7, U110.7, U112.7, U116.9, U116.15, U201.8, U301.10, U302.7, U402.6, U403.7, U406.1, U406.3, U407.10, U501.3, U501.5, U502.3
unnamed: BUS101.25, F101.2
unnamed: BUS101.33, F102.1
unnamed: BUS101.34, F103.1
unnamed: BUS101.50, F104.1
unnamed: C109.2, R116.1, U108.2
unnamed: C405.1, D110.1, R407.2, U403.1
unnamed: C406.1, R411.1
unnamed: C410.1, D403.1, D404.2, R414.1
unnamed: C410.2, C414.1, J403.1, J403.2, R414.2, R415.1, U408.6, U408.7
unnamed: C414.2, D405.2, R415.2, U408.2
unnamed: C415.1, R122.2, R409.1, U402.8
unnamed: C415.2, J401.1, J401.2, R409.2, RV401.2
unnamed: C506.1, R504.2
unnamed: C515.2, R509.2, U504.6, U504.7
unnamed: C516.2, R505.1, U503.3
unnamed: C517.2, R506.1, U503.5
unnamed: C518.2, R507.1, U504.3
unnamed: D110.2, R407.1, U112.4, U116.5, U403.6
unnamed: D301.1, R301.2
unnamed: D301.2, U301.2
unnamed: D302.1, R302.2
unnamed: D302.2, U301.5
unnamed: D303.1, R303.2
unnamed: D303.2, U301.6
unnamed: D304.1, R304.2
unnamed: D304.2, U301.9
unnamed: D305.1, R305.2
unnamed: D305.2, U301.12
unnamed: D306.1, R306.2
unnamed: D306.2, U301.15
unnamed: D307.1, R307.2
unnamed: D307.2, U301.16
unnamed: D308.1, R308.2
unnamed: D308.2, U301.19
unnamed: BlueLight.1, R401.2
unnamed: D403.2, D405.1, U408.1
unnamed: D404.1, R411.2, U406.8, U408.5
unnamed: J107.1, U110.3
unnamed: J107.2, U403.13
unnamed: J109.1, U105.2, U116.4
unnamed: J110.3, R408.2, R412.1
unnamed: J111.1, U105.6, U116.3
unnamed: J112.1, U105.5, U112.6, U116.6
unnamed: J401.3, U402.3
unnamed: J403.3, U116.13
unnamed: J408.1, R404.2, U403.5
unnamed: J411.1, R118.2, U403.11
unnamed: R116.2, U108.3
unnamed: R117.1, U108.4
unnamed: R117.2, U403.3
unnamed: R118.1, U402.7
unnamed: R127.1, U116.8
unnamed: R127.2, U116.10
unnamed: R129.1, U116.2
unnamed: R130.1, U116.12
unnamed: R201.2, U201.6
unnamed: R202.1, U201.5
unnamed: R203.2, U201.4
unnamed: R309.1, U301.1
unnamed: R402.2, U402.5
unnamed: R408.1, U402.2
unnamed: R410.1, U403.8
unnamed: R410.2, U406.6
unnamed: R412.2, U408.3
unnamed: R502.2, R504.1, U501.2
unnamed: R503.1, RV501.2, RV501.3, U501.6
unnamed: R508.1, R512.1, U503.6
unnamed: R510.1, R513.1, U503.2
unnamed: R511.1, R514.1, U504.2
unnamed: U101.1, U201.15
unnamed: U101.3, U201.14
unnamed: U101.5, U201.13
unnamed: U101.9, U201.11
unnamed: U101.11, U201.12
unnamed: U101.13, U112.8
unnamed: U105.1, U110.6, U112.1
unnamed: U105.3, U112.3
unnamed: U105.4, U112.5
unnamed: U105.8, U112.10, U112.12
unnamed: U105.10, U112.13
unnamed: U105.13, U112.11
unnamed: U110.8, U112.2
unnamed: U116.28, U407.4
unnamed: U301.11, U302.8
O1: J108.1, U101.4, U110.2
O2: U101.6, U110.5
O3: U101.10, U110.10
O4: U101.8, U110.13
Phi1: BUS101.38, U105.9
R/~W: BUS101.18, U105.11, U112.9
RD: U101.12, U110.1, U110.4, U110.9, U110.12
WR: U105.12, U302.9
~Armed: BlueLight.2, J406.1, U108.1, U403.9, U407.2
~BufferOE: U110.11, U407.1, U407.19
~DevSel: BUS101.41, R203.1

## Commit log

2017-12-28 Create LICENSE
2017-12-29 fix link
2019-01-09 Changes for Kicad 5
2019-01-09 Gitignore
2019-01-09 Rev. 3 of ADC board, full 12V rail for analog
2019-01-09 Update to footprint library
2019-01-09 ADC Rev. 3 gerber files
2019-01-09 sym lib table
2019-01-09 HV board - KiCad 5 and small footprint changes
2019-04-19 remove gerber files
2019-04-19 minor revision
